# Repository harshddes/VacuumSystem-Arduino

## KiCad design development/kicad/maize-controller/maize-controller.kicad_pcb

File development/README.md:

# MAIZE / test-stand valve controller — start here

> **Current status and decisions:** read [the project status and implementation roadmap](00-project-status.md). All ordered electronics are now reported received. The completed KiCad work covers three bench setups; the full installed-system schematic, field interfaces and operational firmware remain in development.

**Current build: Phase 1, Arduino Uno R3 with the expander bench package.** User reports Uno D5/D6/D7 faulty; leave them disconnected.

1. Start with [the bench package](bench-prep/README.md) and its [module checklist](bench-prep/01-arrival-checklist.md).
2. Build the selected setup using its matching native KiCad drawing, wire IDs and diagnostic sketch.
3. Perform [the bench checks](bench-prep/04-tests.md) and record actual results in [the physical test log](bench-prep/verification/physical-test-log.csv).

The new package uses simulated sensor contacts and LED outputs. It does not release wiring to the Hornet, pilot coils or chamber. The older `02-wires.md` and direct-pin sketch are separate learning baselines; do not combine them with the expander drawing.

## The complete development path

| Phase | What we build | What it proves |
|---|---|---|
| **1 — now** | Buttons, simulated sensors and LEDs | Requests are accepted or rejected correctly; restart requires re-arm |
| 2 | Actual Hornet pressure interface; laptop readout; LED outputs | Real pressure, units, validity and communication faults are handled |
| 3 | One identified cryo gate, field interfaces, position proof and cold/ready input | One real valve can move and respond to faults correctly |
| 4 | Every roughing, vent and pump isolation path; complete physical interlocks | The entire chamber has the required guardrails |
| 5 | Uno sequencing, secured assembly and standalone controls | Pumpdown and vent sequences work without a laptop |

Inventory and identifying connectors are preparation, not a sixth build phase. Automation uses the same permission checks as manual requests. No PLC is required by this prototype plan.

## Documents

- [01 — the plan](01-plan.md)
- [02 — the wires](02-wires.md)
- [03 — the gauge](03-gauge.md)
- [04 — the valves](04-valves.md)
- [05 — the rules](05-rules.md)
- [06 — the tests](06-tests.md)
- [07 — the machines](07-machines.md)
- [08 — still unknown](08-unknowns.md)
- [shopping list](procurement/shopping-list.md), [spreadsheet](procurement/maize-uno-bom.xlsx)
- [Schematics and editable drawing instructions](schematics/README.md)
- [Sources and supplied laboratory guides](references/README.md)
- [Host software tests](tests/README.md), [verification record](verification/host-test-results.txt)

## Document status

This is the finalized **development baseline**, not an as-built wiring release. Known equipment models are incorporated. Unknown gate terminals, temperature signals, chamber volume, allowed pressure thresholds and failure behavior are explicitly tracked. They must be filled with measured or manufacturer-supported values before the corresponding live phase.

The existing repository [Uno references](../docs/README.md) and `pin567_check/` exercise are preserved. This folder supersedes older Nano-based proposals for this project. Start here if older messages disagree with these pin assignments or phases.

This controller requests valve motion and reads equipment readiness. Pump and cryogenic compressor operation stays with the existing equipment controls. Their location in another room does not remove the need for readiness feedback.

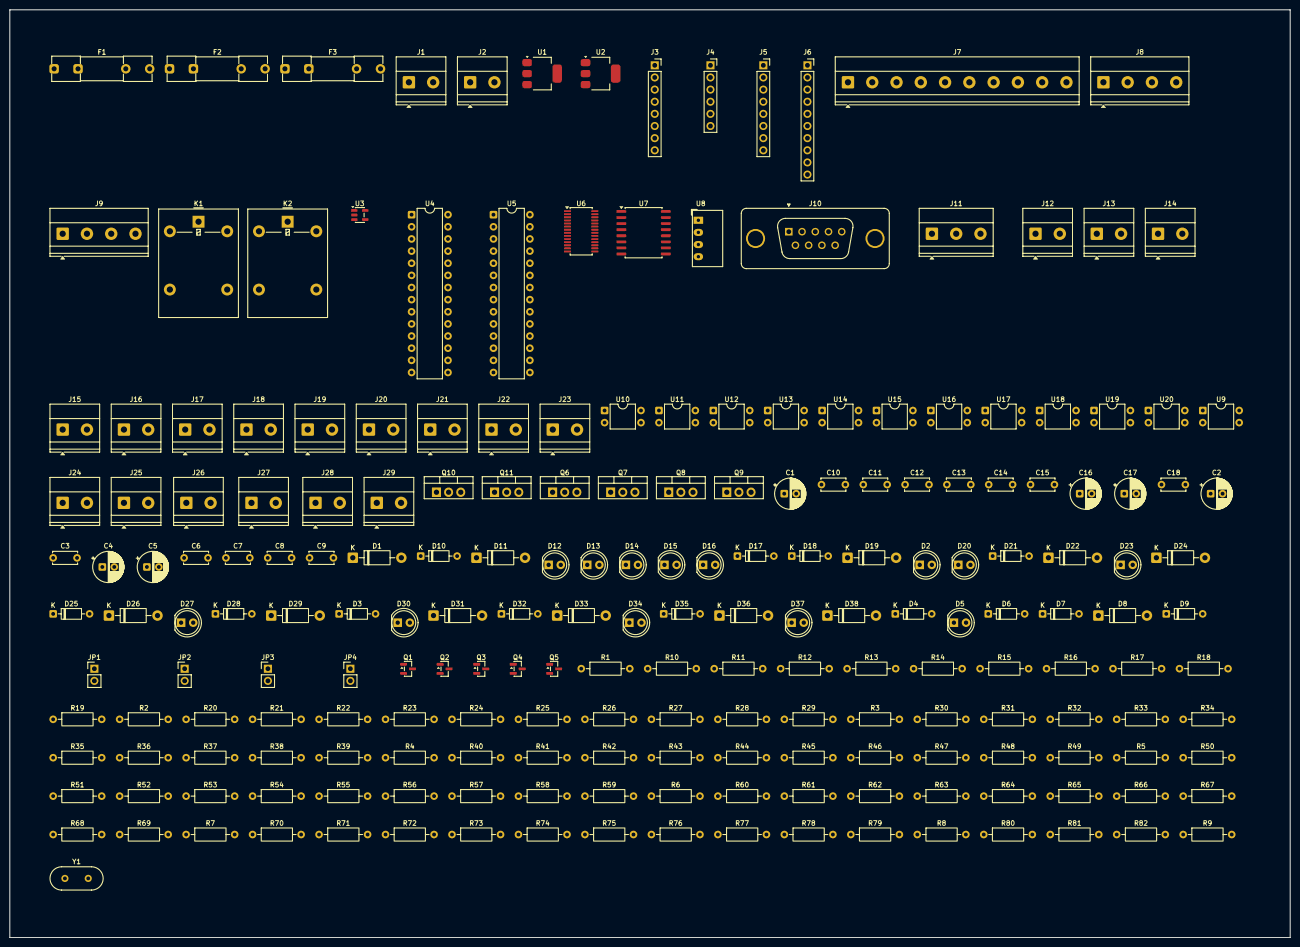
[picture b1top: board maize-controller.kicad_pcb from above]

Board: 2 copper layers, 267.9 x 194.1 mm, 208 parts (0 on the bottom side), 130 nets, no tracks yet.

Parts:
C1: 10uF/25V; CP_Radial_D6.3mm_P2.50mm
C2: 22uF/16V; CP_Radial_D6.3mm_P2.50mm
C3, C6, C7, C8, C9, C10, C11, C12, C15, C18: 100n; C_Disc_D5.0mm_W2.5mm_P5.00mm
C4, C16, C17: 10uF/16V; CP_Radial_D6.3mm_P2.50mm
C5: 22uF/10V; CP_Radial_D6.3mm_P2.50mm
C13, C14: 22p; C_Disc_D5.0mm_W2.5mm_P5.00mm
D1, D8, D11, D19, D22, D24, D26, D29, D31, D33, D36, D38: 1N4007; D_DO-41_SOD81_P10.16mm_Horizontal
D2, D5, D12, D13, D14, D15, D16, D20, D23, D27, D30, D34, D37: LED; LED_D5.0mm
D3, D4: 5.1V; D_DO-35_SOD27_P7.62mm_Horizontal
D6, D7, D17: 1N4148; D_DO-35_SOD27_P7.62mm_Horizontal
D9, D10, D18, D21, D25, D28, D32, D35: 12V; D_DO-35_SOD27_P7.62mm_Horizontal
F1: 500mA; Fuseholder_Clip-5x20mm_Littelfuse_111_Inline_P20.00x5.00mm_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
F2: 3A; Fuseholder_Clip-5x20mm_Littelfuse_111_Inline_P20.00x5.00mm_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
F3: 2A; Fuseholder_Clip-5x20mm_Littelfuse_111_Inline_P20.00x5.00mm_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
J1: J_LOGIC; TerminalBlock_Phoenix_MKDS-1,5-2-5.08_1x02_P5.08mm_Horizont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
J2: J_COIL24; TerminalBlock_Phoenix_MKDS-1,5-2-5.08_1x02_P5.08mm_Horizont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
J3: J_UNO_PWR; PinSocket_1x08_P2.54mm_Vertical
J4: J_UNO_ANALOG; PinSocket_1x06_P2.54mm_Vertical
J5: J_UNO_D0; PinSocket_1x08_P2.54mm_Vertical
J6: J_UNO_D8; PinSocket_1x10_P2.54mm_Vertical
J7: J_PANEL; TerminalBlock_Phoenix_MKDS-1,5-10-5.08_1x10_P5.08mm_Horizon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
J8: J_PANEL_B; TerminalBlock_Phoenix_MKDS-1,5-4-5.08_1x04_P5.08mm_Horizont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
J9: J_DISPLAY; TerminalBlock_Phoenix_MKDS-1,5-4-5.08_1x04_P5.08mm_Horizont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
J10: J_HORNET; DSUB-9_Pins_Vertical_P2.77x2.84mm_MountingHoles
J11: J_HORNET_RELAY_UNCOMMITTED; TerminalBlock_Phoenix_MKDS-1,5-3-5.08_1x03_P5.08mm_Horizont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
J12: J_ZS101C; TerminalBlock_Phoenix_MKDS-1,5-2-5.08_1x02_P5.08mm_Horizont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
J13: J_ZS101O; TerminalBlock_Phoenix_MKDS-1,5-2-5.08_1x02_P5.08mm_Horizont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
J14: J_ZS102C; TerminalBlock_Phoenix_MKDS-1,5-2-5.08_1x02_P5.08mm_Horizont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
J15: J_ZS102O; TerminalBlock_Phoenix_MKDS-1,5-2-5.08_1x02_P5.08mm_Horizont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
J16: J_ZS103C; TerminalBlock_Phoenix_MKDS-1,5-2-5.08_1x02_P5.08mm_Horizont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
J17: J_ZS103O; TerminalBlock_Phoenix_MKDS-1,5-2-5.08_1x02_P5.08mm_Horizont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
J18: J_TI101; TerminalBlock_Phoenix_MKDS-1,5-2-5.08_1x02_P5.08mm_Horizont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
J19: J_PS101; TerminalBlock_Phoenix_MKDS-1,5-2-5.08_1x02_P5.08mm_Horizont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
J20: J_P102; TerminalBlock_Phoenix_MKDS-1,5-2-5.08_1x02_P5.08mm_Horizont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
J21: J_IGOFF; TerminalBlock_Phoenix_MKDS-1,5-2-5.08_1x02_P5.08mm_Horizont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
J22: J_SPARE_A; TerminalBlock_Phoenix_MKDS-1,5-2-5.08_1x02_P5.08mm_Horizont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
J23: J_SPARE_B; TerminalBlock_Phoenix_MKDS-1,5-2-5.08_1x02_P5.08mm_Horizont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
J24: J_CRYO_OPEN; TerminalBlock_Phoenix_MKDS-1,5-2-5.08_1x02_P5.08mm_Horizont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
J25: J_CRYO_CLOSE; TerminalBlock_Phoenix_MKDS-1,5-2-5.08_1x02_P5.08mm_Horizont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
J26: J_ROUGH_OPEN; TerminalBlock_Phoenix_MKDS-1,5-2-5.08_1x02_P5.08mm_Horizont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
J27: J_ROUGH_CLOSE; TerminalBlock_Phoenix_MKDS-1,5-2-5.08_1x02_P5.08mm_Horizont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
J28: J_VENT_OPEN; TerminalBlock_Phoenix_MKDS-1,5-2-5.08_1x02_P5.08mm_Horizont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
J29: J_VENT_CLOSE; TerminalBlock_Phoenix_MKDS-1,5-2-5.08_1x02_P5.08mm_Horizont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
JP1: TERM_120_FIT_TO_ENABLE; PinHeader_1x02_P2.54mm_Vertical
JP2: FORCE_CRYO_CLOSE; PinHeader_1x02_P2.54mm_Vertical
JP3: FORCE_ROUGH_CLOSE; PinHeader_1x02_P2.54mm_Vertical
JP4: FORCE_VENT_CLOSE; PinHeader_1x02_P2.54mm_Vertical
K1, K2: G5LE-1-DC24; Relay_SPDT_Omron-G5LE-1
Q1, Q2, Q3: 2N7002; SOT-23
Q4, Q5: BSS138; SOT-23
Q6, Q7, Q8, Q9, Q10, Q11: IRLZ44N; TO-220-3_Vertical
R1, R29, R30, R31, R32, R33, R67, R70, R73, R76, R79, R82: 2.2k; R_Axial_DIN0207_L6.3mm_D2.5mm_P10.16mm_Horizontal
R2, R4, R9, R10, R11, R13, R15, R17, R37, R66, R69, R72, R75, R78, R81: 100k; R_Axial_DIN0207_L6.3mm_D2.5mm_P10.16mm_Horizontal
R3, R5: 15k; R_Axial_DIN0207_L6.3mm_D2.5mm_P10.16mm_Horizontal
R6, R23, R24, R25, R26, R41, R43, R45, R47, R49, R51, R53, R55, R57, R59, R61, R63: 4.7k; R_Axial_DIN0207_L6.3mm_D2.5mm_P10.16mm_Horizontal
R7, R18, R19, R20, R21, R22, R27, R28, R35, R42, R44, R46, R48, R50, R52, R54, R56, R58, R60, R62, R64: 10k; R_Axial_DIN0207_L6.3mm_D2.5mm_P10.16mm_Horizontal
R8, R12, R14, R16, R34: 1k; R_Axial_DIN0207_L6.3mm_D2.5mm_P10.16mm_Horizontal
R36: 1M; R_Axial_DIN0207_L6.3mm_D2.5mm_P10.16mm_Horizontal
R38, R39: 680; R_Axial_DIN0207_L6.3mm_D2.5mm_P10.16mm_Horizontal
R40: 120; R_Axial_DIN0207_L6.3mm_D2.5mm_P10.16mm_Horizontal
R65, R68, R71, R74, R77, R80: 100; R_Axial_DIN0207_L6.3mm_D2.5mm_P10.16mm_Horizontal
U1: AMS1117-5.0; SOT-223-3_TabPin2
U2: AMS1117-3.3; SOT-223-3_TabPin2
U3: TPS3823-33; SOT-23-5
U4: MCP23017_OUT_0x20; DIP-28_W7.62mm
U5: MCP23017_IN_0x21; DIP-28_W7.62mm
U6: SC16IS752IPW; TSSOP-28_4.4x9.7mm_P0.65mm
U7: ISO3082DW; SOIC-16W_7.5x10.3mm_P1.27mm
U8: CRE1S0505SC; Converter_DCDC_Murata_CRE1xxxxxxSC_THT
U9, U10, U11, U12, U13, U14, U15, U16, U17, U18, U19, U20: PC817; DIP-4_W7.62mm
Y1: 1.8432MHz; Crystal_HC49-U_Vertical

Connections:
+3V3: C5.1, C6.1, C12.1, C15.1, Q4.1, Q5.1, R24.2, R26.2, R34.2, R35.2, U2.2, U6.8, U6.9, U6.10, U6.11, U7.1
+5V: C2.1, C3.1, C4.1, C7.1, C10.1, C11.1, C16.1, J7.2, J9.2, R1.1, R7.2, R18.2, R19.2, R20.2, R21.2, R22.2, R23.2, R25.2, R27.2, R28.2, R42.2, R44.2, R46.2, R48.2, R50.2, R52.2, R54.2, R56.2, R58.2, R60.2, R62.2, R64.2, U1.2, U2.3, U3.5, U4.9, U5.9, U5.15, U8.2
+5V_ISO: C17.1, C18.1, R38.1, U7.16, U8.4
+9V: C1.1, D1.1, J3.8, U1.3
+9V_RAW: F1.1, J1.1
+9V_SW: D1.2, F1.2
+24V_CLOSE: D22.1, D29.1, D36.1, F3.2, J25.1, J27.1, J29.1
+24V_FUSED: D8.1, D11.1, F2.2, F3.1, J12.1, J13.1, J14.1, J15.1, J16.1, J17.1, J18.1, J19.1, J20.1, J21.1, J22.1, J23.1, K1.1, K1.2, K2.1, R2.1
+24V_OPEN: D19.1, D26.1, D33.1, J24.1, J26.1, J28.1, K1.3, R4.1, R6.1
+24V_RAW: F2.1, J2.1
ARM_BTN: J6.1, J8.2, R21.1
BUS_A: J10.9, JP1.1, R38.2, U7.12
BUS_B: J10.6, R39.1, R40.2, U7.13
CRYO_REQ: J5.6, J7.9, R18.1
DRAIN_CRYO_CLOSE: D22.2, J25.2, JP2.1, Q7.2
DRAIN_CRYO_OPEN: D19.2, J24.2, Q6.2
DRAIN_ROUGH_CLOSE: D29.2, J27.2, JP3.1, Q9.2
DRAIN_ROUGH_OPEN: D26.2, J26.2, Q8.2
DRAIN_VENT_CLOSE: D36.2, J29.2, JP4.1, Q11.2
DRAIN_VENT_OPEN: D33.2, J28.2, Q10.2
ENABLE_GATE: D9.1, Q1.1, R12.2, R13.1
ENABLE_RAW: D6.1, D7.1, J7.6
ENABLE_SW: J7.7, R9.1, R12.1
FORCE_BUS: D24.1, D31.1, D38.1, K2.2
FORCE_GATE: Q3.1, R16.2, R17.1
FORCE_MID_CRYO_CLOSE: D24.2, JP2.2
FORCE_MID_ROUGH_CLOSE: D31.2, JP3.2
FORCE_MID_VENT_CLOSE: D38.2, JP4.2
GATE_CRYO_CLOSE: D21.1, Q7.1, R68.2, R69.1
GATE_CRYO_OPEN: D18.1, Q6.1, R65.2, R66.1
GATE_ROUGH_CLOSE: D28.1, Q9.1, R74.2, R75.1
GATE_ROUGH_OPEN: D25.1, Q8.1, R71.2, R72.1
GATE_VENT_CLOSE: D35.1, Q11.1, R80.2, R81.1
GATE_VENT_OPEN: D32.1, Q10.1, R77.2, R78.1
GND: C1.2, C2.2, C3.2, C4.2, C5.2, C6.2, C7.2, C8.2, C9.2, C10.2, C11.2, C12.2, C13.2, C14.2, C15.2, C16.2, D2.1, D3.2, D4.2, D5.1, D9.2, D10.2, D12.1, D13.1, D14.1, D15.1, D16.1, D18.2, D20.1, D21.2, D23.1, D25.2, D27.1, D28.2, D30.1, D32.2, D34.1, D35.2, D37.1, J1.2, J2.2, J3.6, J3.7, J6.7, J7.1, J8.4, J9.1, K2.4, Q2.2, Q3.2, Q6.3, Q7.3, Q8.3, Q9.3, Q10.3, Q11.3, R3.2, R5.2, R9.2, R10.2, R11.2, R13.2, R15.2, R17.2, R37.2, R66.2, R69.2, R72.2, R75.2, R78.2, R81.2, U1.1, U2.1, U3.2, U4.10, U4.15, U4.16, U4.17, U5.10, U5.16, U5.17, U6.2, U6.16, U6.22, U6.24, U7.2, U7.7, U7.8, U8.1, U9.2, U9.3, U10.2, U10.3, U11.2, U11.3, U12.2, U12.3, U13.2, U13.3, U14.2, U14.3, U15.2, U15.3, U16.2, U16.3, U17.2, U17.3, U18.2, U18.3, U19.2, U19.3, U20.2, U20.3
GND_ISO: C17.2, C18.2, J10.4, R39.2, U7.9, U7.10, U7.15, U8.3
GPIO_CRYO_CLOSE: R68.1, R70.1, U4.22
GPIO_CRYO_OPEN: R65.1, R67.1, U4.21
GPIO_LED_ARMED: R30.1, U4.28
GPIO_LED_ARMED_LED: D13.2, R30.2
GPIO_LED_FAULT: R29.1, U4.27
GPIO_LED_FAULT_LED: D12.2, R29.2
GPIO_LED_SEQ: R31.1, U4.8
GPIO_LED_SEQ_LED: D14.2, R31.2
GPIO_ROUGH_CLOSE: R74.1, R76.1, U4.24
GPIO_ROUGH_OPEN: R71.1, R73.1, U4.23
GPIO_SPARE0: R32.1, U4.1
GPIO_SPARE0_LED: D15.2, R32.2
GPIO_SPARE1: R33.1, U4.2
GPIO_SPARE1_LED: D16.2, R33.2
GPIO_VENT_CLOSE: R80.1, R82.1, U4.26
GPIO_VENT_OPEN: R77.1, R79.1, U4.25
HORNET_RLY_1: J10.1, J11.1
HORNET_RLY_5: J10.5, J11.2
HORNET_RLY_7: J10.7, J11.3
INT_IN: J5.3, R28.1, U5.19, U5.20
IN_IGOFF: R60.1, U5.3, U18.4
IN_P102: R58.1, U5.2, U17.4
IN_PS101: R56.1, U5.1, U16.4
IN_SPARE_A: R62.1, U5.4, U19.4
IN_SPARE_B: R64.1, U5.5, U20.4
IN_TI101: R54.1, U5.27, U15.4
IN_ZS101C: R42.1, U5.21, U9.4
IN_ZS101O: R44.1, U5.22, U10.4
IN_ZS102C: R46.1, U5.23, U11.4
IN_ZS102O: R48.1, U5.24, U12.4
IN_ZS103C: R50.1, U5.25, U13.4
IN_ZS103O: R52.1, U5.26, U14.4
KFORCE_LOW: D11.2, K2.5, Q3.3
KOPEN_LOW: D8.2, K1.5, Q1.3
KOPEN_MID: Q1.2, Q2.3
LED_5V: D2.2, R1.2
LED_CRYO_CLOSE: D23.2, R70.2
LED_CRYO_OPEN: D20.2, R67.2
LED_OPEN_A: D5.2, R6.2
LED_ROUGH_CLOSE: D30.2, R76.2
LED_ROUGH_OPEN: D27.2, R73.2
LED_VENT_CLOSE: D37.2, R82.2
LED_VENT_OPEN: D34.2, R79.2
MODE_AUTO: D7.2, J6.5, J7.5, R11.1
MODE_MAN: D6.2, J6.4, J7.4, R10.1
OPTO_A_0: R41.2, U9.1
OPTO_A_1: R43.2, U10.1
OPTO_A_2: R45.2, U11.1
OPTO_A_3: R47.2, U12.1
OPTO_A_4: R49.2, U13.1
OPTO_A_5: R51.2, U14.1
OPTO_A_6: R53.2, U15.1
OPTO_A_7: R55.2, U16.1
OPTO_A_8: R57.2, U17.1
OPTO_A_9: R59.2, U18.1
OPTO_A_10: R61.2, U19.1
OPTO_A_11: R63.2, U20.1
OUT_INT: R27.1, U4.19, U4.20
ROUGH_REQ: J5.7, J7.10, R19.1
RS485_DE: R37.1, U6.18, U7.4, U7.5
SCL_3V3: Q5.2, R26.1, U6.13
SCL_5V: J4.6, J6.10, J9.4, Q5.3, R25.1, U4.12, U5.12
SDA_3V3: Q4.2, R24.1, U6.14
SDA_5V: J4.5, J6.9, J9.3, Q4.3, R23.1, U4.13, U5.13
SENSE_24V: D3.1, J4.1, R2.2, R3.1
SENSE_OPEN: D4.1, J4.2, R4.2, R5.1
SIG_0: J12.2, R41.1
SIG_1: J13.2, R43.1
SIG_2: J14.2, R45.1
SIG_3: J15.2, R47.1
SIG_4: J16.2, R49.1
SIG_5: J17.2, R51.1
SIG_6: J18.2, R53.1
SIG_7: J19.2, R55.1
SIG_8: J20.2, R57.1
SIG_9: J21.2, R59.1
SIG_10: J22.2, R61.1
SIG_11: J23.2, R63.1
START_BTN: J6.3, J8.3, R22.1
STOP_NODE: J6.2, J7.8, R7.1, U3.3
TERM_MID: JP1.2, R40.1
UART_IRQ: J5.4, R34.1, U6.15
UART_RESET: D17.2, R35.1, U6.5
UART_RX: U6.4, U7.3
UART_TX: U6.3, U7.6
UNO_3V3: C9.1, J3.4
UNO_5V: C8.1, J3.5
VENT_REQ: J5.8, J8.1, R20.1
WDI: R8.2, U3.4
WDI_UNO: J5.5, R8.1
WD_GATE: D10.1, Q2.1, R14.2, R15.1
WD_OK: D17.1, R14.1, R16.1, U3.1, U4.18, U5.18
XTAL1: C13.1, R36.1, U6.6, Y1.1
XTAL2: C14.1, R36.2, U6.7, Y1.2

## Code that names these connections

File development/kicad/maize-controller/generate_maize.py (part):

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        capacitor(sheet, "100n", "+5V", "GND")

    expander("MCP23017_OUT_0x20", {
        "GPB0": "GPIO_SPARE0",
        "GPB1": "GPIO_SPARE1",
        "GPB2": None,
        "GPB3": None,
        "GPB4": None,
        "GPB5": None,
        "GPB6": None,
        "GPB7": "GPIO_LED_SEQ",
        "VDD": "+5V",
        "VSS": "GND",
        "NC": None,
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        "RESET": "WD_OK",
        "INTB": "OUT_INT",
        "INTA": "OUT_INT",
        "GPA0": "GPIO_CRYO_OPEN",
        "GPA1": "GPIO_CRYO_CLOSE",
        "GPA2": "GPIO_ROUGH_OPEN",
        "GPA3": "GPIO_ROUGH_CLOSE",
        "GPA4": "GPIO_VENT_OPEN",
        "GPA5": "GPIO_VENT_CLOSE",
        "GPA6": "GPIO_LED_FAULT",
        "GPA7": "GPIO_LED_ARMED",
    })
    resistor(sheet, "10k", "OUT_INT", "+5V")
    sheet.newline()
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    sheet.newline()

    # Status LEDs driven by the output expander. Command lamps, not position proof.
    for net in ("GPIO_LED_FAULT", "GPIO_LED_ARMED", "GPIO_LED_SEQ", "GPIO_SPARE0", "GPIO_SPARE1"):
        anode = net + "_LED"
        resistor(sheet, "2.2k", net, anode)
        led(sheet, anode)
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        "IRQ": "UART_IRQ",
        "CTSB": "GND",
        "RTSB": None,
        "GPIO0/DSRB": "RS485_DE",
        "GPIO1/DTRB": None,
        "GPIO2/CDB": None,
        "GPIO3/RIB": None,
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    )
    sheet.newline()
    drivers = [
        ("CRYO_OPEN", "GPIO_CRYO_OPEN", "+24V_OPEN", False),
        ("CRYO_CLOSE", "GPIO_CRYO_CLOSE", "+24V_CLOSE", True),
        ("ROUGH_OPEN", "GPIO_ROUGH_OPEN", "+24V_OPEN", False),
        ("ROUGH_CLOSE", "GPIO_ROUGH_CLOSE", "+24V_CLOSE", True),
        ("VENT_OPEN", "GPIO_VENT_OPEN", "+24V_OPEN", False),
        ("VENT_CLOSE", "GPIO_VENT_CLOSE", "+24V_CLOSE", True),
    ]
    for index, (tag, gpio, high, force) in enumerate(drivers):
        gate = f"GATE_{tag}"
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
